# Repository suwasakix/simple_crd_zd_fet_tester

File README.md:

# Simple CRD/ZD/FET Tester

定電流ダイオード/定電圧ダイオード/FET 簡易測定器

&nbsp;

## 目次 - Contents

 - [このプリント基板について](#このプリント基板について---about-this-pcb)
 - [ガーバーデータのダウンロード](#ガーバーデータのダウンロード---download-gerber-data)
 - [回路図](#回路図---pcb-schematic)
 - [レイアウト](#レイアウト---pcb-layout)
 - [部品リスト](#部品リスト---parts-list)
 - [便利なアイテム](#便利なアイテム---useful-items)
 - [使用例](#使用例---example-of-use)
 - [開発環境](#開発環境---development-environment)
 - [ライセンスについて](#ライセンスについて---license)

&nbsp;

## このプリント基板について - About this PCB

このプリント基板は、ぺるけさんの [6AH4GT 全段差動プッシュプル・アンプ](http://www.op316.com/tubes/myamp/6ah4pp.htm) のページで紹介されている定電流ダイオード(CRD)・定電圧ダイオード(ZD)・FETの簡易測定回路を１枚の基板にまとめたものです。  

この基板では、CRD の電流値、ZD のツェナー電圧、J-FET の Idss およびバイアスの測定ができます。  

この基板は CRD、ZD、FET の簡易測定を目的としたものであり、自作のアンプに使用する半導体部品を選別するのに向いています。選別した半導体部品を第三者に頒布することを目的とする場合は、電流と電圧の両方を調整できるような高機能な測定器が必要になると思います。  

&nbsp;

## ガーバーデータのダウンロード - Download gerber data

こちらのページから「simple_crd_zd_fet_tester-gerber.zip」のファイルをダウンロードしてください。  

&emsp; https://www.github.com/suwasakix/simple_crd_zd_fet_tester/releases

このプロジェクトは、各自がプリント基板のガーバーデータをダウンロードして PCB 基板メーカーに基板製造を発注することを前提にしています。個人で発注可能な PCB 基板メーカーは国内外問わずありますが、近年では 10cm 四方以下の基板サイズであれば海外メーカーで格安に製造委託することが可能になりました。発注例として、深圳の Seeed studio が提供する PCB 製造サービス「[Fusion PCB](https://www.fusionpcb.jp)」に基板製造を発注する方法を[こちらのページ](docs/ORDER_PCB.md)で紹介しておきます。

本リポジトリの Release で公開しているガーバーデータは、Fusion PCB に発注して問題なく基板が製造されることを確認しております。

&nbsp;

## 回路図 - PCB schematic

CRD/ZD/FET の選別をしたことがある方には特に説明の必要もない回路ですが、使い方が分からない方は[使用例](#使用例---example-of-use)に目を通していただければと思います。

R1, R2 は電流値を測定するための抵抗なので高精度品か、あるいは抵抗値を実測してなるべく 1kΩ / 100Ω に近いものを使用してください。

VR1 ～ VR6 は FET のバイアス調整用の半固定ボリュームです。半固定ボリュームは実機回路のバランスを調整するために使われる部品で一旦調整が完了したら動かさないことから、一般的に半固定ボリュームの回転寿命は長くありません（ボリュームの回転を繰り返しているうちに接触面が劣化して抵抗値の調整ができなくなります）。本来であれば回転寿命がより長いボリュームを割り当てるべきですが、本基板は自作アンプの部品選別することが目的なので、使用頻度が多くなることはないだろうと判断して割り切りました。最初は VR1 と VR2 を使って、それらがダメになったら VR3 と VR4 を使って、その次に VR5 と VR6 で……と、半固定ボリュームは消耗品扱いの前提で使用しています。

電源には 9V または 12V の AC アダプターを使用してください。DC ジャックは 外径 5.5mm / 内径 2.1mm センタープラスのものが適合します。9V 角型電池に DC プラグ付 9V 電池スナップを接続して使ってもかまいません。

&nbsp;

## レイアウト - PCB layout

* 基板サイズ : W 80mm × H 60mm

&nbsp;

## 部品リスト - Parts list

* 通販による部品販売では、10個単位などでまとめ売りされている場合がしばしばあります。注文の際にはご注意ください。
* ☆ は使用しなければ省略可。

|部品種別			|記号					|部品名															|値				|個数		|入手ルート																												|
|:----:				|:----:					|:----:															|:----:			|:----:		|:----:																													|
|抵抗				|R1						|金属皮膜抵抗 1/4W												|1kΩ			|1			|[高精度 金属皮膜抵抗 1/2W1kΩ ±0.1%][AK_108510_R1k]<br>[高精度 金属皮膜抵抗 1/4W1kΩ ±0.1%][AK_108505_R1k]			|
|					|R2						|金属皮膜抵抗 1/4W												|100Ω			|1			|[高精度 金属皮膜抵抗 1/2W100Ω ±0.1%][AK_108509_R100]<br>[高精度 金属皮膜抵抗 1/4W100Ω ±0.1%][AK_108504_R100]		|
|半固定抵抗			|VR1 ～ VR3 ☆			|半固定抵抗<br>(FETバイアス粗調整用)							|1kΩ			|1 ～ 3		|[半固定ボリューム GF063P 1kΩ][AK_114901_VR1k]																			|
|					|VR4 ～ VR6 ☆			|半固定抵抗<br>(FETバイアス微調整用)							|100Ω			|1 ～ 3		|[半固定ボリューム GF063P 100Ω][AK_114897_VR100]																		|
|コンデンサ			|C1						|電解コンデンサ<br>(直径 6.3mm,<br>リードピッチ 2.5mm)			|100μF			|1			|[100μF35V105℃ ルビコンZLH][AK_102724_C35v100u]																		|
|スイッチ			|SW1					|4極 DIPスイッチ												|-				|1			|[DIPスイッチ 4P KSD42][AK_108923_SW_KSD42]																				|
|チェック端子		|TP1 ～ TP11 ☆			|チェック端子													|-				|8			|[チェック端子][AK_C_CCHECKTER]																							|
|ソケット			|J1						|基板型DCジャック<br>(内径2.1mm, 外径5.5mm)						|-				|1			|[MJ-179P][AK_100077_MJ-179P]<br>[2DC0005D100 1パック4個入][AK_101604_2DC0005D100]										|
|					|J2, J3 ☆				|8ピン 板バネICソケット											|-				|2			|[2227-08-03 1パック10個入][AK_100017_2227-08-03]																		|
|基板スペーサー		|						|黄銅六角スペーサー<br>M3×10mm									|-				|4			|[FB3-10][AK_107313_FB3-10]																								|
|					|						|M3 ネジ								 						|-				|4			|(ホームセンター等で入手可能)																							|

[AK_108510_R1k]:								https://akizukidenshi.com/catalog/g/g108510/
[AK_108505_R1k]:								https://akizukidenshi.com/catalog/g/g108505/
[AK_108509_R100]:								https://akizukidenshi.com/catalog/g/g108509/
[AK_108504_R100]:								https://akizukidenshi.com/catalog/g/g108504/
[AK_114901_VR1k]:								https://akizukidenshi.com/catalog/g/g114901/
[AK_114897_VR100]:								https://akizukidenshi.com/catalog/g/g114897/
[AK_102724_C35v100u]:							https://akizukidenshi.com/catalog/g/g102724/
[AK_108923_SW_KSD42]:							https://akizukidenshi.com/catalog/g/g108923/
[AK_C_CCHECKTER]:								https://akizukidenshi.com/catalog/c/ccheckter/
[AK_100077_MJ-179P]:							https://akizukidenshi.com/catalog/g/g100077/
[AK_101604_2DC0005D100]:						https://akizukidenshi.com/catalog/g/g101604/
[AK_100017_2227-08-03]:							https://akizukidenshi.com/catalog/g/g100017/
[AK_107313_FB3-10]:								https://akizukidenshi.com/catalog/g/g107313/

R1, R2 は金属皮膜抵抗の高精度品を使用するか、あるいは誤差±1%の金属皮膜抵抗から選別したものを割り当てます。普及価格帯のデジタルマルチメーターの場合、抵抗値の確度（測定誤差）はおおよそ ±0.5% ～ ±1.0% といったところなので、高精度品を使用した方が外れは少ないことになります。ただし、高精度品を使用する場合でも部品の不良チェックのために抵抗値は実測しておくようにしてください。

FET のバイアス測定を行わない場合、VR1 ～ VR6 は不要です。少なくとも VR1, VR2 のみを実装すればバイアス測定は可能です。

J2, J3 は FET 用のソケットです。使わないソケットは省略することもできます。TP9 ～ TP11 から線出しして IC クリップで測定する FET を繋いでもよいです。

ショート事故防止のため、必ず基板スペーサーを付けて使用してください。

&nbsp;

## 便利なアイテム - Useful items

|部品名																			|入手ルート																																				|
|:----:																			|:----:																																					|
|ACアダプター 12V<br>(DCプラグ内径2.1mm, 外径5.5mm,<br>センタープラス)			|[M120100-A010JP][AK_117429_ACDC12V_M120100-A010JP]<br>[AD-M120P100][AK_111994_ACDC12V_AD-M120P100]<br>[AD-K120P100][AK_106642_ACDC12V_AD-K120P100]		|
|DCプラグ付9V電池スナップ<br>(DCプラグ内径2.1mm, 外径5.5mm,<br>センタープラス)	|[BS-IR-1][AK_107356_DCP_BS-IR-1]																														|
|テストリード<br>(バナナプラグ ⇔ ICクリップ)									|[TLA-106][AK_112359_TLA-106]																															|
|テストリード<br>(ICクリップ両端)												|[TLA-105][AK_112419_TLA-105]<br>[TLA-101][AK_111765_TLA-101]																							|

[AK_117429_ACDC12V_M120100-A010JP]:				https://akizukidenshi.com/catalog/g/g117429/
[AK_111994_ACDC12V_AD-M120P100]:				https://akizukidenshi.com/catalog/g/g111994/
[AK_106642_ACDC12V_AD-K120P100]:				https://akizukidenshi.com/catalog/g/g106642/
[AK_107356_DCP_BS-IR-1]:						https://akizukidenshi.com/catalog/g/g107356/
[AK_112359_TLA-106]:							https://akizukidenshi.com/catalog/g/g112359/
[AK_112419_TLA-105]:							https://akizukidenshi.com/catalog/g/g112419/
[AK_111765_TLA-101]:							https://akizukidenshi.com/catalog/g/g111765/

&nbsp;

## 使用例 - Example of use

### 定電流ダイオード (CRD) の測定

テスターを CRD+ と CRD- の端子に、定電流ダイオードを CRD/ZD の両端子に接続します。

テスターに表示された電圧値 (V) が定電流ダイオードの電流値 (mA) になります。

&nbsp;

### 定電圧ダイオード (ZD) の測定

テスターと定電流ダイオードの両方を CRD/ZD の両端子に接続します。

テスターに表示された電圧値 (V) が定電圧ダイオードのツェナー電圧 (V) になります。

&nbsp;

### FET のドレイン飽和電流 (Idss) の測定

DIP スイッチの SW1 のみを ON にした状態で、テスターを FET+ と FET- の端子に接続し、FET をソケットに差し込みます。

テスターに表示された電圧値 (mV) を 100で割った（小数点を左に２桁スライドさせた）値が FET のドレイン飽和電流 (mA) になります。

&nbsp;

### FET のドレイン電流 - バイアスの測定

ドレイン飽和電流と同様ですが、DIP スイッチは SW2 ～ SW4 のいずれかに合わせてください。

SW に対応した半固定抵抗を操作してバイアスを調整すると、バイアス電圧とドレイン電流の関係を調べることができます。

この方法は FET を使って定電流回路を作るときに必要な抵抗値を調べるのに役立ちます（抵抗値を測定する際には必ず基板の電源を抜いてください）。

&nbsp;

## 開発環境 - Development environment

このプリント基板の設計データは、[KiCad](https://www.kicad.org) 9.0 で作成しています。基板のデータは KiCad 9.0 以降で編集することができます。  

なお、この基板のデータを改変するには KiCad ライブラリ [Victwale](https://github.com/suwasakix/Victwale) を必要とします。  

&nbsp;

## ライセンスについて - License

このプリント基板の設計データのライセンスは [Creative Commons CC-BY 4.0 License](https://creativecommons.org/licenses/by/4.0/legalcode) です。

- 上記設計データの著作権は作者 (suwasakix) が保持します。ただし、著作権が生じるのは設計データのレイアウトのみであり、回路図に著作権は生じません。

- 上記設計データは、何の制限もなく私的に利用することができます。データを自由に改変して私的に利用することもできます。

- 上記設計データに変更を加えることなく製造したプリント基板は、商用・非商用を問わず何の制限もなく第三者に頒布することができます。

- 上記設計データの改変物、または改変物をもとに製造したプリント基板（二次創作物）を第三者に頒布するには、原作品が著作権者 (suwasakix) のものであること、および当該作品が二次創作物であることを明示する必要があります。一例としては、原作品の著作権者、および二次創作物の著作権者を当該作品に明示すれば問題ありません。

  - なお、それらを明示する手段は当該作品の実物以外に、当該作品の設計データの一時配布元でもよいものとします（当該作品に著作権者の情報を記載する物理的なスペースがない場合には、一時配布元に著作権者の情報を記載することで代えることが可能です）。その場合、当該作品の実物にデータの一時配布元が記載されていなければなりません。

- 上記設計データの二次創作物には、原作品とは異なるライセンスを適用することができます。

- 上記ライセンスは著作権者からの一方的な利用許諾条件です。利用するにあたり著作権者への連絡は一切不要です。

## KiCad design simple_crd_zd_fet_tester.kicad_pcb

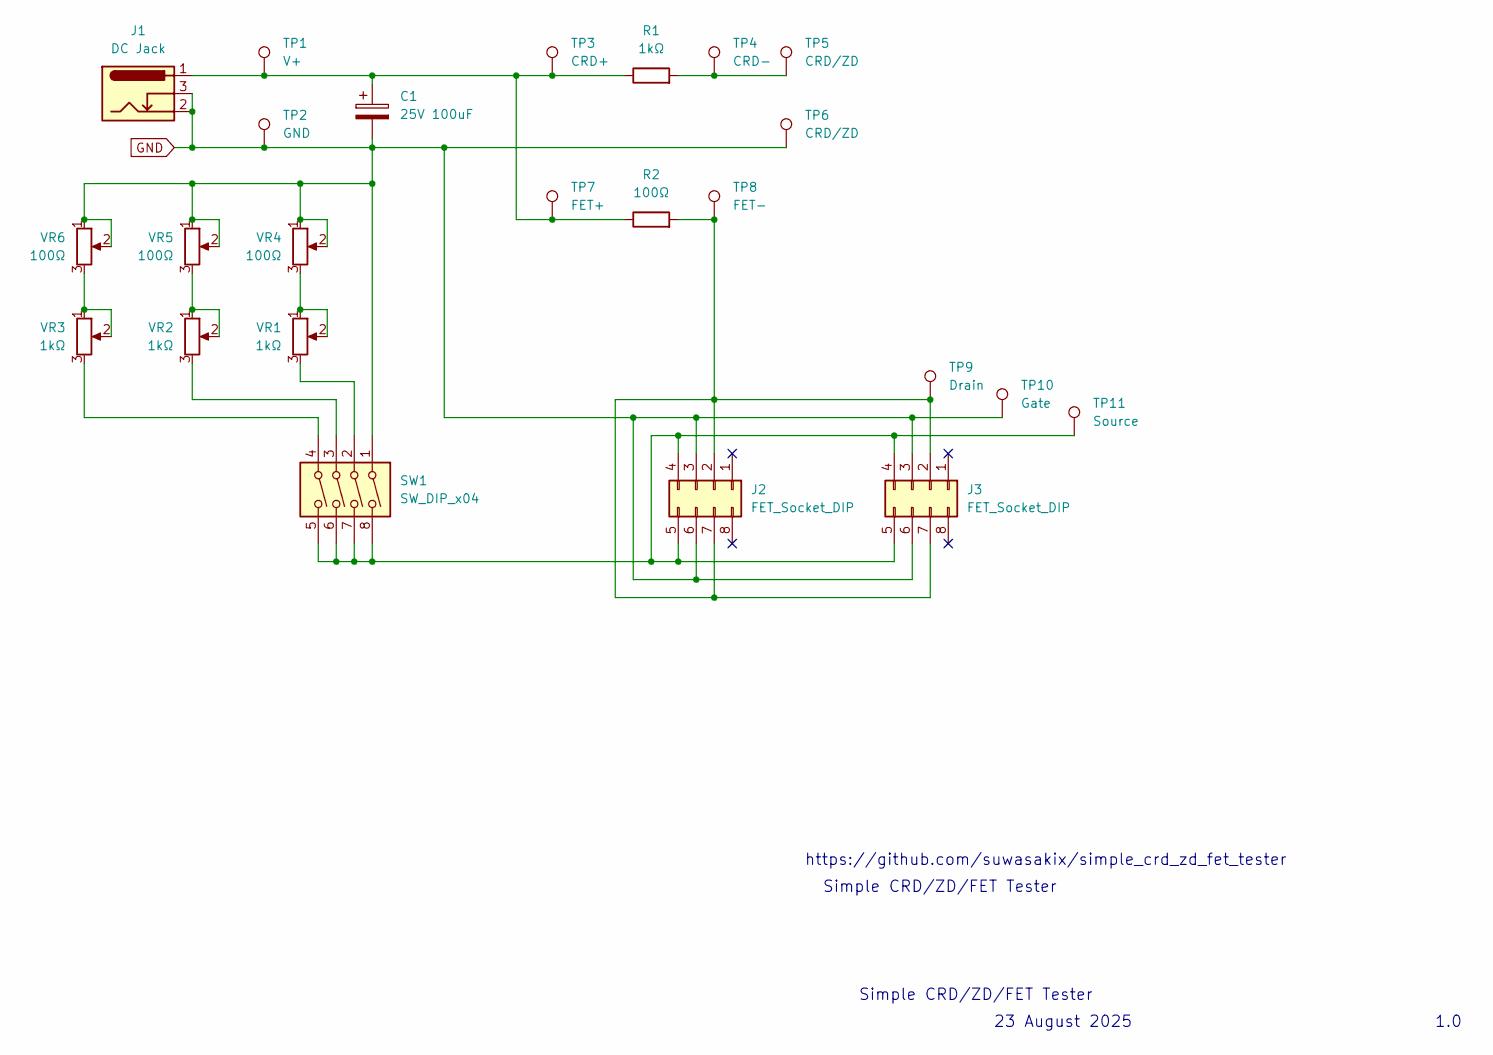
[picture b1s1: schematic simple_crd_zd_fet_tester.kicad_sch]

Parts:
C1: 25V 100uF; CP_Radial_D6.3mm_P2.50mm
J1: DC Jack; BarrelJack_Horizontal
J2, J3: FET_Socket_DIP; DIP-8_W7.62mm_Socket
R1: 1kΩ; R_Axial_DIN0411_L9.9mm_D3.6mm_P12.70mm_Horizontal
R2: 100Ω; R_Axial_DIN0411_L9.9mm_D3.6mm_P12.70mm_Horizontal
SW1: SW_DIP_x04; SW_DIP_SPSTx04_Slide_6.7x11.72mm_W7.62mm_P2.54mm_LowProfile
TP1: V+; Pin_D1.0mm_L10.0mm
TP2: GND; Pin_D1.0mm_L10.0mm
TP3: CRD+; Pin_D1.0mm_L10.0mm
TP4: CRD-; Pin_D1.0mm_L10.0mm
TP5, TP6: CRD/ZD; Pin_D1.0mm_L10.0mm
TP7: FET+; Pin_D1.0mm_L10.0mm
TP8: FET-; Pin_D1.0mm_L10.0mm
TP9: Drain; Pin_D1.0mm_L10.0mm
TP10: Gate; Pin_D1.0mm_L10.0mm
TP11: Source; Pin_D1.0mm_L10.0mm
VR1, VR2, VR3: 1kΩ; Potentiometer_Vishay_T73YP_Vertical
VR4, VR5, VR6: 100Ω; Potentiometer_Vishay_T73YP_Vertical

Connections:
GND: C1.2, J1.2, J1.3, J2.3, J2.6, J3.3, J3.6, SW1.1, TP2.1, TP6.1, TP10.1, VR4.1, VR4.2, VR5.1, VR5.2, VR6.1, VR6.2
unnamed: C1.1, J1.1, R1.1, R2.1, TP1.1, TP3.1, TP7.1
unnamed: J2.2, J2.7, J3.2, J3.7, R2.2, TP8.1, TP9.1
unnamed: J2.4, J2.5, J3.4, J3.5, SW1.5, SW1.6, SW1.7, SW1.8, TP11.1
unnamed: R1.2, TP4.1, TP5.1
unnamed: SW1.2, VR1.3
unnamed: SW1.3, VR2.3
unnamed: SW1.4, VR3.3
unnamed: VR1.1, VR1.2, VR4.3
unnamed: VR2.1, VR2.2, VR5.3
unnamed: VR3.1, VR3.2, VR6.3

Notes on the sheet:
Simple CRD/ZD/FET Tester
23 August 2025
https://github.com/suwasakix/simple_crd_zd_fet_tester
1.0

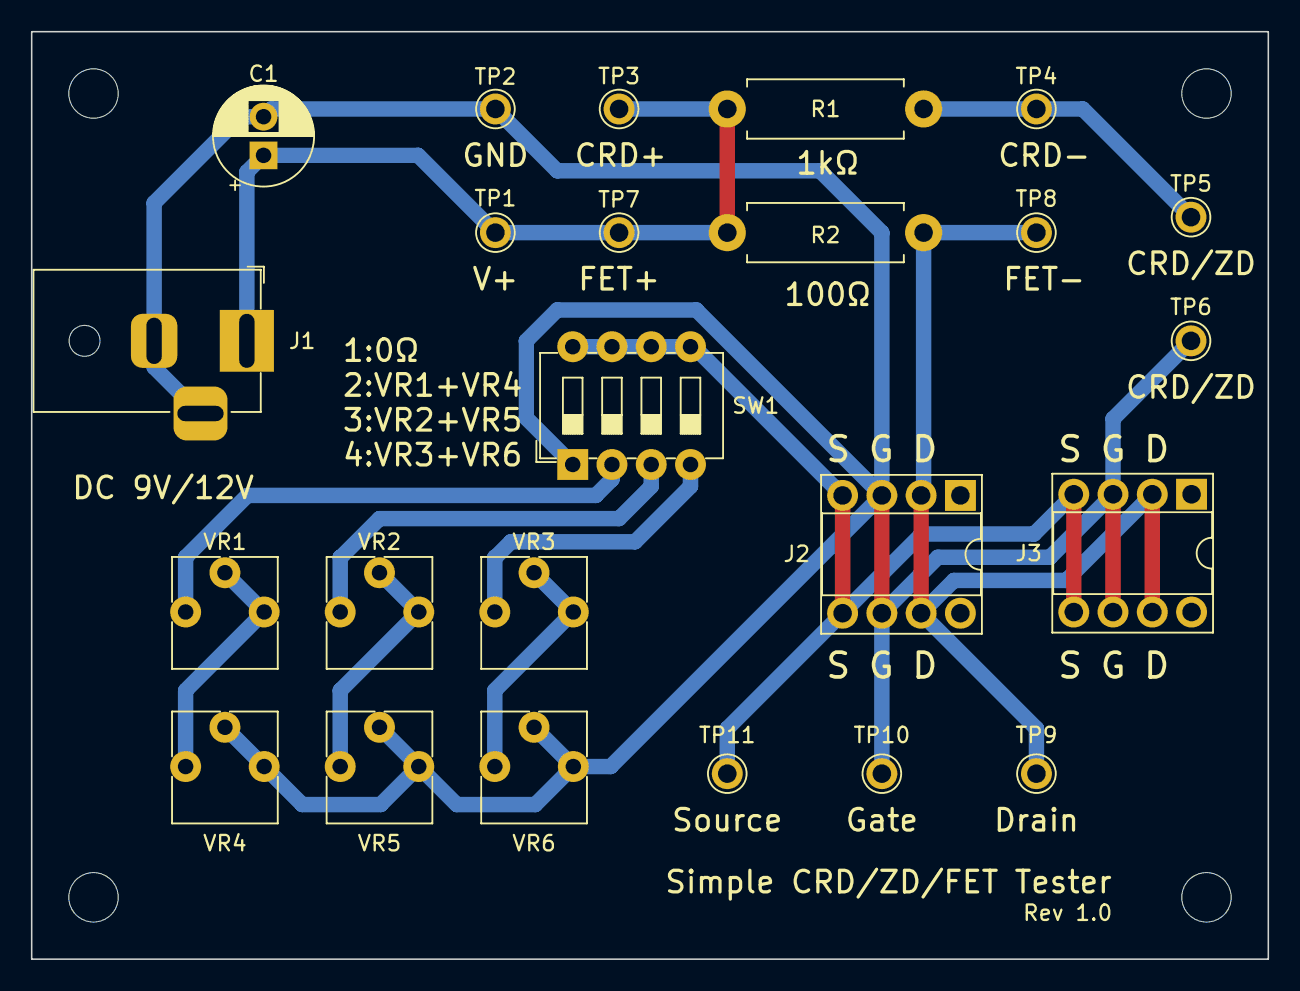
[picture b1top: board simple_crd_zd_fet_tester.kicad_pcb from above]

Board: 2 copper layers, 80.0 x 60.0 mm, 24 parts (0 on the bottom side), 11 nets.

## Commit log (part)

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2025-09-15 First release
    * based on KiCAD 9.0
2025-12-17 Update documents
    * Add LICENSE
    * Update README.md

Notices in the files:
simple_crd_zd_fet_tester.kicad_pcb:
© suwasakix 2025, licensed under CC-BY-4.0
